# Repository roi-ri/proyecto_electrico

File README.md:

# Proyecto Eléctrico - Ciclador de Baterías

Repositorio integral del proyecto de diseño, construcción y validación de un
ciclador de baterías de propósito múltiple. El proyecto reúne el hardware de
potencia y medición, el firmware de control, el protocolo de comunicación y una
aplicación de escritorio para operar pruebas, visualizar telemetría y exportar
resultados.

## Descripción general

El sistema está orientado a ejecutar pruebas controladas de carga, descarga y
ciclado sobre baterías. La arquitectura combina una PCB dedicada, un ESP32 como
unidad de control y adquisición, sensores de corriente y tensión, y la
aplicación `batView` para supervisar el proceso desde una computadora.

Los objetivos principales del repositorio son:

- Centralizar la documentación técnica y administrativa del proyecto.
- Mantener el diseño eléctrico y los archivos de fabricación de la PCB.
- Versionar el firmware encargado del control y la comunicación.
- Desarrollar la aplicación de escritorio para operación, monitoreo y
  exportación de datos.
- Conservar cronogramas, bitácoras y propuestas como evidencia del avance.

## Componentes del sistema

| Componente | Ubicación | Descripción |
|---|---|---|
| Aplicación de escritorio | `batView/` | Interfaz en C++/wxWidgets para controlar pruebas vía USB/UART, graficar telemetría y exportar resultados. |
| Firmware/control | `code/` | Código en C para control PI, monitoreo de carga/descarga, límites de tensión y comunicación con la PC. |
| PCB | `PCB/` | Proyecto KiCad con esquemático, layout, huellas, símbolos, modelos 3D, salidas e imágenes del diseño. |
| Propuesta | `propuesta/` | Descripción inicial del ciclador, diagramas y documentos de diseño por área. |
| Cronograma | `cronograma/` | Plan de trabajo semanal del proyecto. |
| Bitácoras | `bitácora/` | Registro individual de avances, decisiones y actividades. |

## Estructura del repositorio

```text
proyecto_electrico/
|
├── README.md                         documentación principal del repositorio
├── LICENSE                           licencia MIT del proyecto
├── .gitignore                        reglas generales de archivos ignorados
├── .gitmodules                       submódulos utilizados por el repositorio
|
├── batView/                          aplicación de escritorio del proyecto
│   ├── README.md                     guía técnica de batView
│   ├── CMakeLists.txt                configuración de compilación y pruebas
│   ├── build_app.sh                  build completo para macOS/Linux
│   ├── build_app.ps1                 build completo para Windows
│   ├── install_macos.sh              instalación y empaquetado en macOS
│   ├── install_linux.sh              instalación y empaquetado en Linux
│   ├── install_windows.ps1           instalación y empaquetado en Windows
│   ├── src/                          código fuente de la aplicación
│   ├── tests/                        pruebas unitarias
│   ├── docs/                         documentación de arquitectura e instalación
│   ├── examples/                     firmware de prueba para ESP32
│   ├── scripts/                      automatización de build
│   └── assets/                       iconos e imágenes de la aplicación
|
├── code/                             firmware y control embebido
│   ├── include/                      encabezados del firmware
│   └── src/                          implementaciones en C
|
├── PCB/                              diseño electrónico en KiCad
│   ├── README.md                     documentación de la PCB
│   ├── Proyecto.kicad_pro            archivo principal del proyecto KiCad
│   ├── Proyecto.kicad_sch            esquemático eléctrico
│   ├── Proyecto.kicad_pcb            layout de la PCB
│   ├── symbols/                      símbolos personalizados
│   ├── footprints/                   huellas personalizadas
│   ├── 3dmodels/                     modelos 3D de componentes
│   ├── outputs/                      salidas generadas del diseño
│   └── Imagenes/                     vistas y capturas del diseño
|
├── propuesta/                        propuesta y documentos iniciales
│   ├── propuesta.md                  planteamiento general
│   ├── images/                       diagramas e imágenes de apoyo
│   ├── programa_sw/                  documentación del software
│   ├── protocolo_comunicacion/       documentación del protocolo
│   └── ciclador/                     documentación del ciclador
|
├── cronograma/                       planificación temporal
│   └── cronograma.md                 cronograma semanal
|
└── bitácora/                         bitácoras individuales del equipo
    ├── Brandon.md
    ├── Edu.md
    ├── Jose.md
    ├── Luis.md
    └── Rodrigo.md
```

## Flujo de trabajo del sistema

1. La PCB integra las etapas de potencia, acondicionamiento, sensado y conexión
   con el ESP32.
2. El firmware del ESP32 ejecuta el control de carga/descarga, monitorea
   variables eléctricas y aplica límites de seguridad.
3. La PC se comunica con el ESP32 mediante USB/UART usando tramas de protocolo
   definidas para conexión, configuración, carga, descarga, ciclado y paro.
4. `batView` envía comandos, recibe telemetría, muestra el estado de la prueba,
   grafica mediciones y exporta datos para análisis posterior.

## Protocolo de comunicación

La aplicación y el ESP32 intercambian mensajes de texto con prefijo `#`. Entre
las tramas principales utilizadas por `batView` se encuentran:

- `#CONNECTION`
- `#Battery,<BatteryNameID>,<V@max>,<V@min>,<Amax>`
- `#CICLE,0,0`
- `#CICLE,1,<numeroCiclos>`
- `#LOAD,<0-100>`
- `#UNLOAD,<0-100>`
- `#STOP`
- `#DATA,<tensión>,<corriente>,<timestamp>`

La documentación detallada del protocolo y del flujo de la aplicación se
encuentra en [`batView/README.md`](batView/README.md) y en
[`propuesta/protocolo_comunicacion/`](propuesta/protocolo_comunicacion/).

## Requisitos principales

### Software de escritorio

Para compilar y ejecutar `batView` se requiere, según el sistema operativo:

- CMake.
- Compilador C++ compatible.
- wxWidgets.
- Python 3 y dependencias de empaquetado/exportación.
- Git.

Guías específicas:

- [Instalación en macOS](batView/docs/INSTALL_MACOS.md)
- [Instalación en Linux](batView/docs/INSTALL_LINUX.md)
- [Instalación en Windows](batView/docs/INSTALL_WINDOWS.md)

### Diseño electrónico

Para abrir o modificar la PCB se recomienda:

- KiCad.
- Librerías locales incluidas en `PCB/symbols/`, `PCB/footprints/` y
  `PCB/3dmodels/`.

### Firmware

Para trabajar con el código embebido se recomienda contar con:

- Toolchain compatible con ESP32 o entorno equivalente.
- Acceso al puerto USB/UART del microcontrolador.
- Instrumentación básica para validar tensión, corriente y polaridad antes de
  conectar baterías reales.

## Puesta en marcha rápida

1. Clonar el repositorio:

```bash
git clone <URL_DEL_REPOSITORIO>
cd proyecto_electrico
```

2. Revisar la documentación de la PCB:

```bash
open PCB/README.md
```

3. Entrar a la aplicación de escritorio:

```bash
cd batView
```

4. Ejecutar el instalador correspondiente al sistema:

```bash
./install_macos.sh
```

En Linux:

```bash
./install_linux.sh
```

En Windows:

```powershell
powershell -ExecutionPolicy Bypass -File .\install_windows.ps1
```

## Documentación recomendada

- [`batView/README.md`](batView/README.md): guía principal de la aplicación,
  arquitectura, protocolo, build, pruebas y exportación.
- [`PCB/README.md`](PCB/README.md): descripción de la PCB, conectores, sensores,
  capas y recomendaciones de conexión.
- [`propuesta/propuesta.md`](propuesta/propuesta.md): planteamiento general del
  proyecto.
- [`cronograma/cronograma.md`](cronograma/cronograma.md): actividades planeadas
  por semana.
- [`bitácora/`](bitácora/): seguimiento individual del avance del equipo.

## Estado del proyecto

El repositorio contiene una base funcional y documentada para el desarrollo del
ciclador:

- Aplicación `batView` con conexión serial, flujo guiado de pruebas, gráficas y
  exportación.
- Proyecto KiCad de PCB con documentación visual y descripción de conectores.
- Código de control con módulos separados para comunicación, control PI,
  monitoreo, límites de tensión y paro.
- Documentación académica de propuesta, cronograma y bitácoras.

## Buenas prácticas de uso

- Validar polaridad y niveles de tensión antes de conectar una batería real.
- Probar primero con fuentes limitadas en corriente o cargas controladas.
- Mantener separadas las salidas generadas localmente de los archivos fuente.
- Registrar cambios relevantes en las bitácoras correspondientes.
- Actualizar la documentación cuando se modifique el protocolo, la PCB o el
  flujo de operación de `batView`.

## Licencia

Este proyecto se distribuye bajo licencia MIT. Consulte [`LICENSE`](LICENSE)
para ver los términos completos.

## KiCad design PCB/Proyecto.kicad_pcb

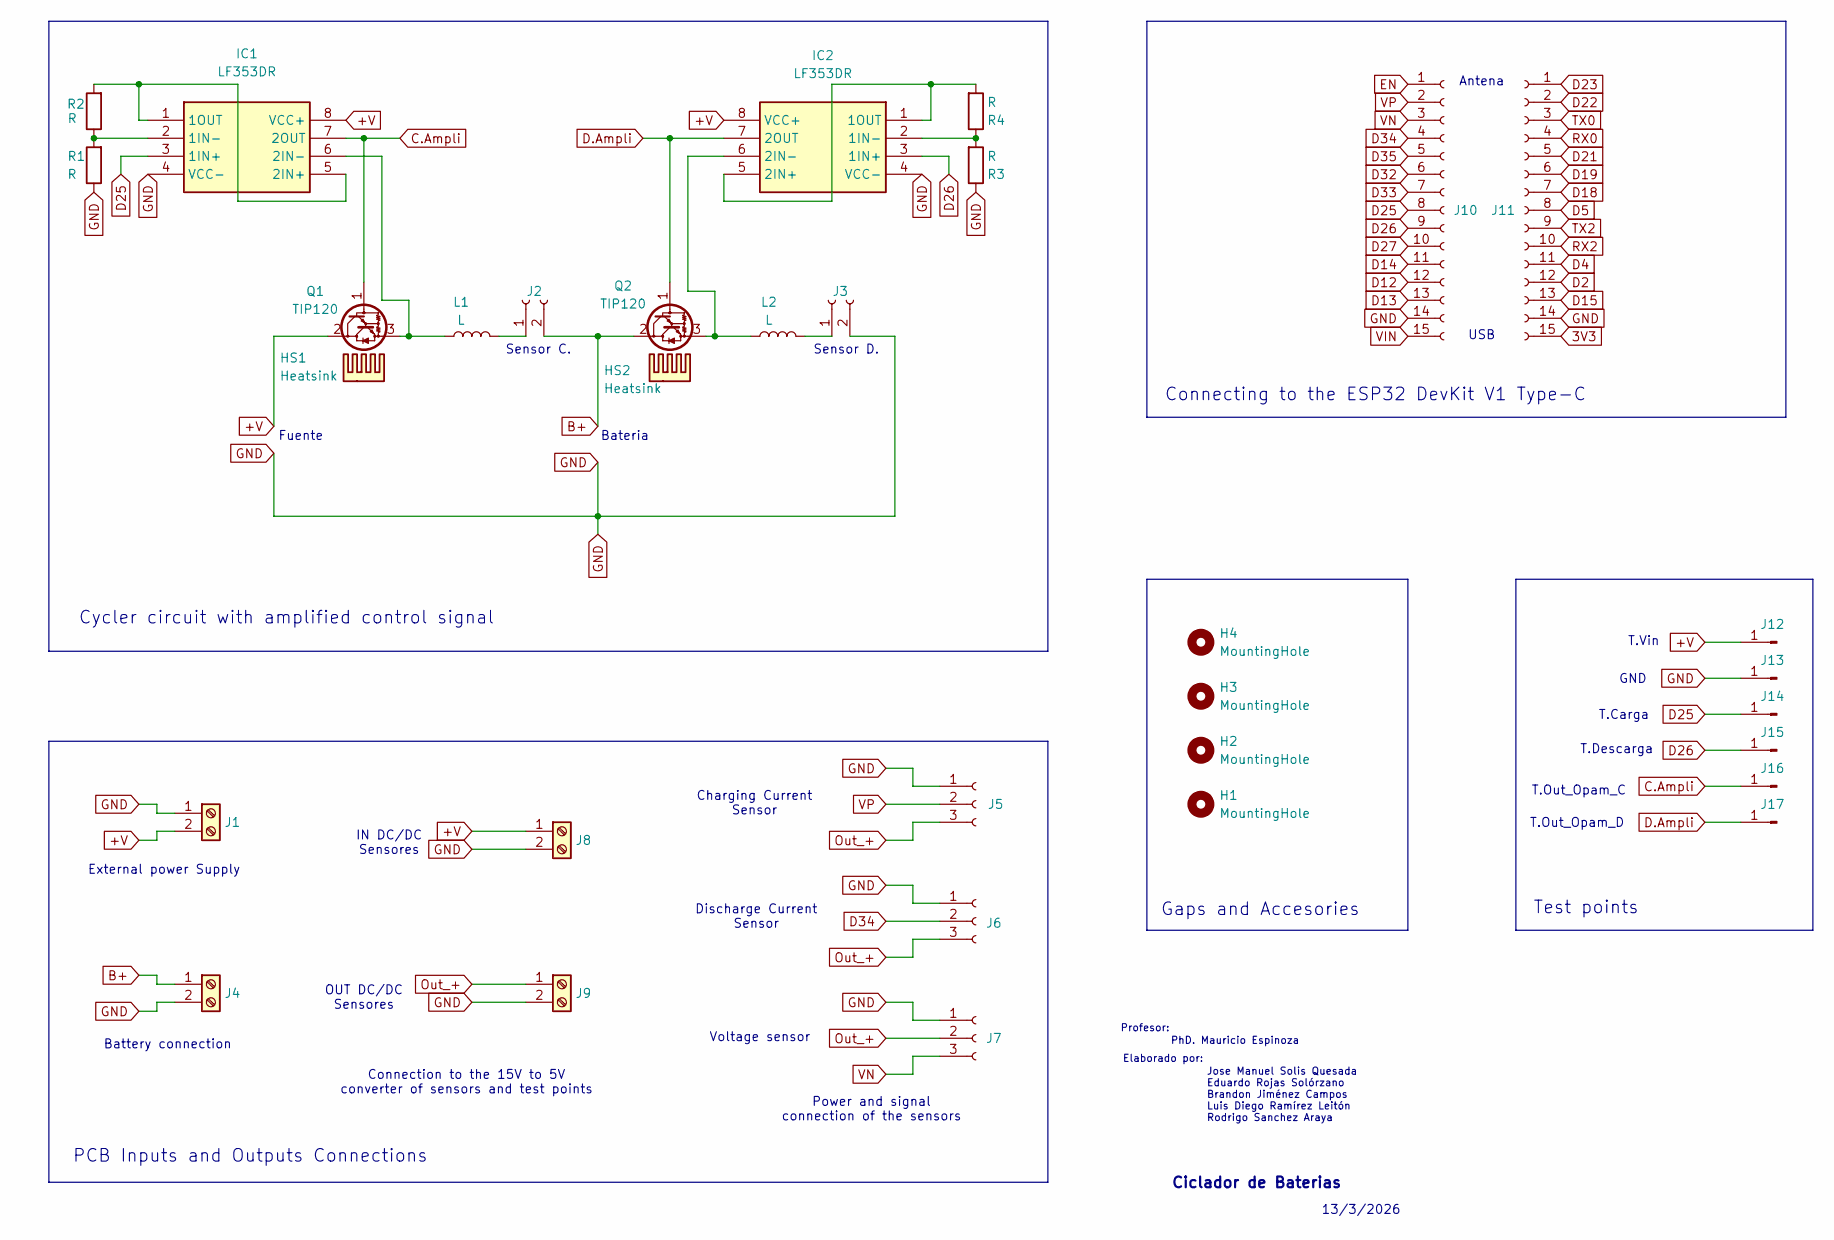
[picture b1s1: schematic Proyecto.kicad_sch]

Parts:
H1, H2, H3, H4: MountingHole; MountingHole_3.2mm_M3
HS1, HS2: Heatsink; Heatsink_TO220_Vert_20x15x11_Pin0
IC1, IC2: LF353DR; SOIC127P600X175-8N; Mouser Part Number 595-LF353DR
J1: Screw_Terminal_01x02; BarrelJack_GCT_DCJ200-10-A_Horizontal
J2, J3: Conn_01x02_Socket; PinSocket_1x02_P2.54mm_Vertical
J4: Screw_Terminal_01x02; TerminalBlock_Phoenix_MKDS-1,5-2_1x02_P5.00mm_Horizontal
J5, J6, J7: Conn_01x03_Socket; PinSocket_1x03_P2.54mm_Vertical
J8, J9: Screw_Terminal_01x02; TerminalBlock_Phoenix_MPT-0,5-2-2.54_1x02_P2.54mm_Horizontal
J10, J11: Conn_01x15_Socket; PinSocket_1x15_P2.54mm_Vertical
J12, J13, J14, J15, J16, J17: Conn_01x01_Pin; TestPoint_Loop_D2.54mm_Drill1.5mm_Beaded
L1, L2: L; L_Radial_D7.8mm_P5.00mm_Fastron_07HCP
Q1, Q2: TIP120; TO-220-3_Vertical
R1, R2, R3, R4: R; R_1206_3216Metric_Pad1.30x1.75mm_HandSolder

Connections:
3V3: J11.15
+V: IC1.8 (VCC+), IC2.8 (VCC+), J1.2, J8.1, J12.1, Q1.2 (C)
B+: J2.2, J4.1, Q2.2 (C)
C.Ampli: IC1.7 (2OUT), J16.1, Q1.1 (B)
D2: J11.12
D4: J11.11
D5: J11.8
D12: J10.12
D13: J10.13
D14: J10.11
D15: J11.13
D18: J11.7
D19: J11.6
D21: J11.5
D22: J11.2
D23: J11.1
D25: IC1.3 (1IN+), J10.8, J14.1
D26: IC2.3 (1IN+), J10.9, J15.1
D27: J10.10
D32: J10.6
D33: J10.7
D34: J6.2, J10.4
D35: J10.5
D.Ampli: IC2.7 (2OUT), J17.1, Q2.1 (B)
EN: J10.1
GND: IC1.4 (VCC-), IC2.4 (VCC-), J1.1, J3.2, J4.2, J5.1, J6.1, J7.1, J8.2, J9.2, J10.14, J11.14, J13.1, R1.1, R3.1
unnamed: IC1.2 (1IN-), R1.2, R2.1
unnamed: IC1.1 (1OUT), IC1.5 (2IN+), R2.2
unnamed: IC1.6 (2IN-), L1.1, Q1.3 (E)
unnamed: IC2.2 (1IN-), R3.2, R4.1
unnamed: IC2.1 (1OUT), IC2.5 (2IN+), R4.2
unnamed: IC2.6 (2IN-), L2.1, Q2.3 (E)
unnamed: J2.1, L1.2
unnamed: J3.1, L2.2
Out_+: J5.3, J6.3, J7.2, J9.1
RX0: J11.4
RX2: J11.10
TX0: J11.3
TX2: J11.9
VIN: J10.15
VN: J7.3, J10.3
VP: J5.2, J10.2

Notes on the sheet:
Jose Manuel Solis Quesada Eduardo Rojas Solórzano Brandon Jiménez Campos Luis Diego Ramírez Leitón Rodrigo Sanchez Araya
Antena
13/3/2026
Charging Current Sensor
Elaborado por:
T.Descarga
Bateria
Sensor D.
T.Out_Opam_C
Profesor:
Cycler circuit with amplified control signal
Ciclador de Baterias
IN DC/DC Sensores
Voltage sensor
Fuente
Sensor C.
GND
PhD. Mauricio Espinoza
Connecting to the ESP32 DevKit V1 Type-C
Battery connection
T.Out_Opam_D
PCB Inputs and Outputs Connections
T.Vin
Connection to the 15V to 5V converter of sensors and test points
T.Carga
Power and signal connection of the sensors
Test points
USB
Discharge Current Sensor
OUT DC/DC Sensores
Gaps and Accesories
External power Supply

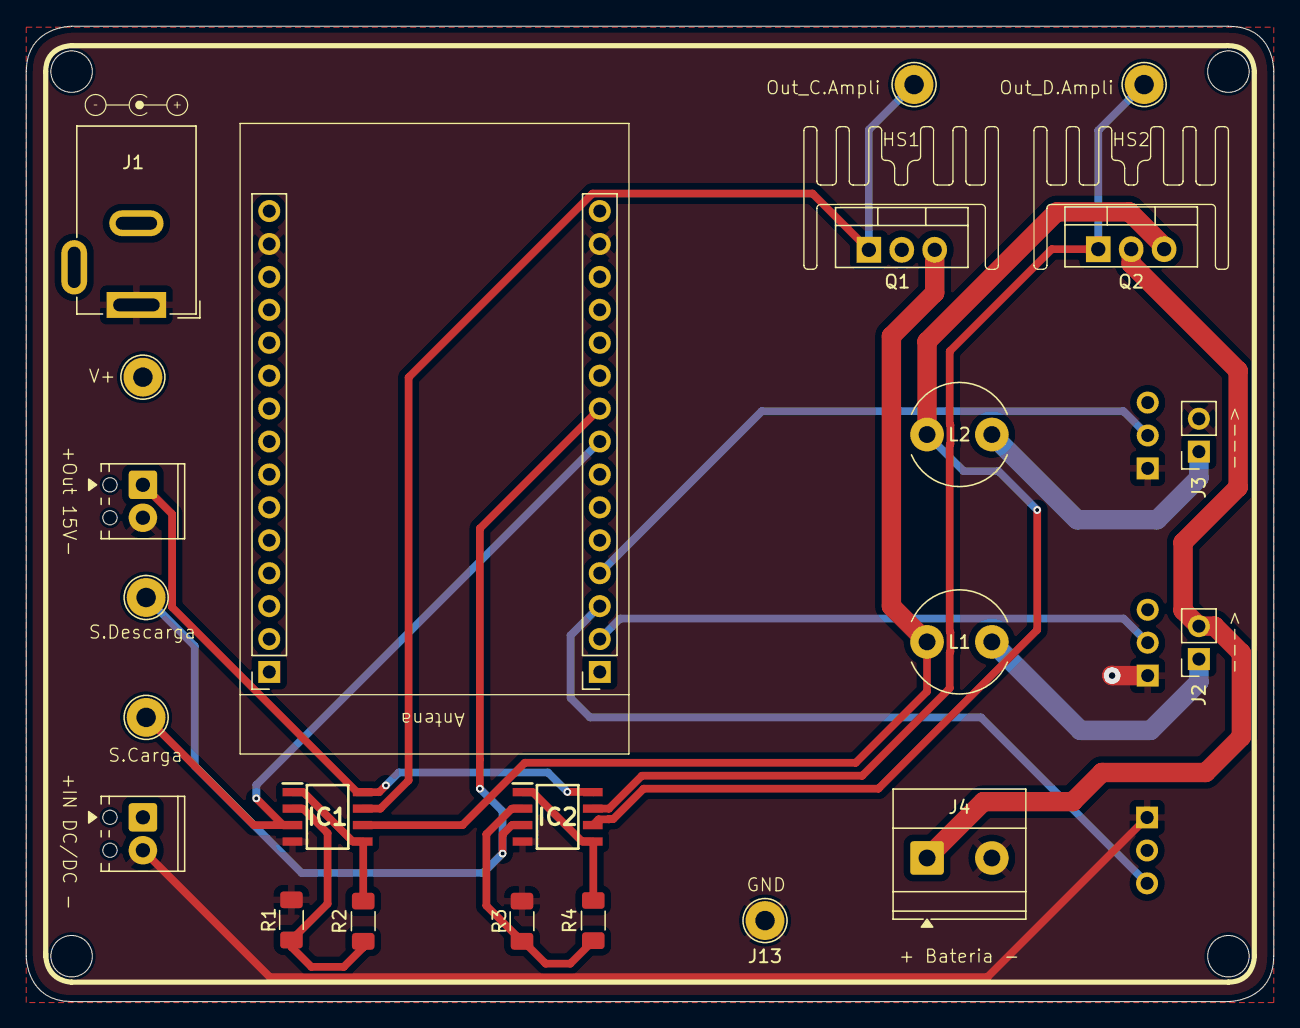
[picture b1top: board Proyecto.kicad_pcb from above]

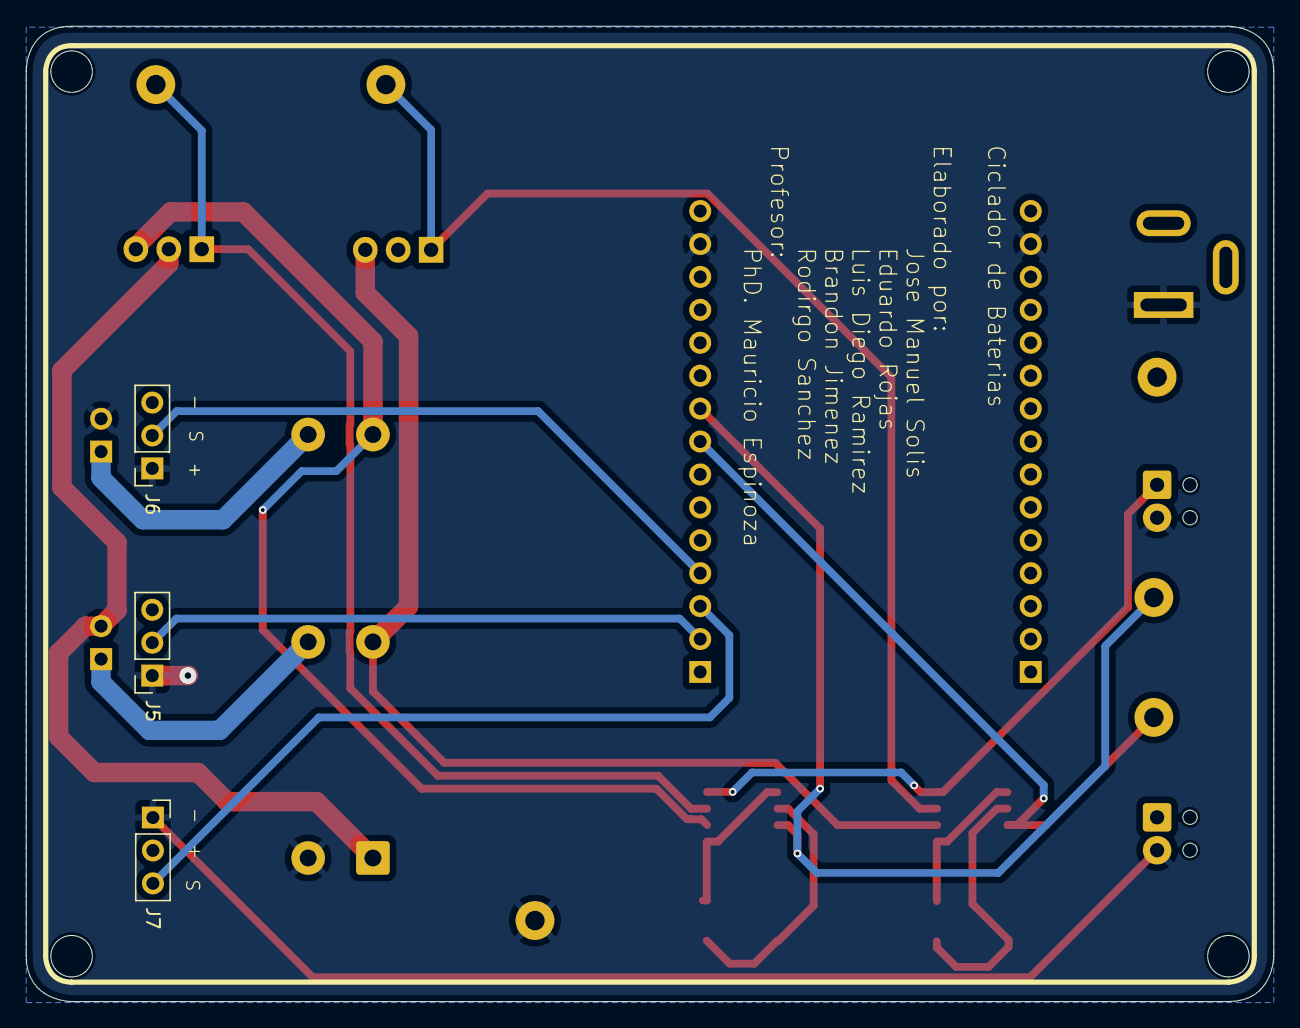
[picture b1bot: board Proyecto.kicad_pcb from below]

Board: 4 copper layers, 96.2 x 75.3 mm, 33 parts (3 on the bottom side), 19 nets.

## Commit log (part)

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2026-02-03 Added: diagrama propuesta
2026-02-04 Added: Directorio para estipular propuesta inicial del ciclador
2026-02-04 Added: Directorio para estipular propuesta inicial del sw
2026-02-04 Added: Directorio para estipular propuesta inicial del protocolo de comunicacion hw <-> sw
2026-02-10 Prueba
2026-02-11 docs: actualizar README con propuesta del ciclador
2026-02-11 docs: añadir README para PCB y PLECS en ciclador
2026-02-11 docs: actualización de README para PCB y PLECS en ciclador
2026-02-17 Added: bitácora para guardar lo que se va haciendo
2026-02-17 Added: branch del ciclador
2026-02-17 Added: Alcances y limitaciones de la aplicación y definición de las arquitecturas para realizar dicho SW
2026-02-17 Added: Arquitectura lógica por capas para la propuesta seleccionada para realizar el SW
2026-02-17 Fix: link formatting in README.md
2026-02-18 Added: Primera actividad realizada en bitácora
2026-02-18 Update link in Rodrigo.md for Propuesta_SW
2026-02-21 Added: link para basar el uso de la GUI con wxWidgets
2026-03-02 Added: Cronograma en el cuál se estarán colocando las actividades esperadas a realizar semana con semana para el pryecto eléctrico
2026-03-02 Fixed: se elimina cronograma de este branch
2026-03-02 Added: cronograma para colocar objetivos a realizar por semana durante el proyecto
2026-03-03 Se agrega la tabla completa, faltan agregar los contenidos
2026-03-03 Added: Se agregan actividades a realizar hasta semana 6
2026-03-09 Added: Se agrega el inicio de la propuesta del protocolo de comu
2026-03-09 Fix: Detalle en título
2026-03-10 Added: Finalización de la propuesta
2026-03-10 feature: Se agrega la bitacora del 10-3-2025
2026-03-10 Feature: Corrección en el formato de la tabla
2026-03-10 Added: Se agrega en la bitácora lo trabajado el día 10 de Marzo
2026-03-10 Added: Se agrega en la bitácora lo trabajado el día 9 de Marzo
2026-03-11 Fixed: Arreglo de tabla de componentes.
2026-03-11 Added: Tabla de presupuestos.
2026-03-11 Fix: Corrección de formato de tabla y actividades
2026-03-15 Added: Bitácora.
2026-03-15 Fixed: Arreglo en la bitácora.
2026-03-15 Fixed: Arreglo en el formato de la fecha de la bitácora.
2026-03-15 Fixed: Arreglos en la bitácora.
2026-03-16 Se agregan los códigos para la obtención de los datos de los sensores
2026-03-16 Fixed: Arreglo en el presupuesto
2026-03-16 Added: sección de requisitos fundamentales y Envío de datos al ESP32
2026-03-17 Added: Se agregan actividades realizadas a la bitácora.
2026-03-17 Fixed: Correción del formato de la tabla la bitácora.
2026-03-17 Fixed: Correción del formato de la tabla.
2026-03-30 Added: Actualización de la bitácora del proyecto
2026-03-30 Fixed: Se corriege el formato de la tabla.
2026-03-31 Added: Uso de WxWidgets para crear apliaciones, utilizando el OS de Mac
2026-04-01 Added: Se agrega propuesta final para la creación del programa de SW
2026-04-01 Added: Redirección en el README hacia el archivo de propuesta final
2026-04-01 Fix link formatting in README.md
2026-04-01 Added: contenido realizado en las últimas semanas a la bitácora
2026-04-02 FIX: Migración a librería actualizada de ESP
2026-04-02 FIX: Se agrega un bitwidth de 12 para mayor seguridad
2026-04-09 Added: Update de la bitácora
2026-04-13 Test: Prueba de orden.
2026-04-13 Fixed: Arreglo en las pruebas.
2026-04-22 Added: estrucutra de la aplicación + segunda y primera capa de integración de esta, con funcionalidades cruciales para la gestión de la adquisisción de datos, la validación del protocolo, la enumerac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
2026-04-22 Se integraron los servicios de adquisición y los paneles para mostrar los resultados en tiempo real. Implementamos las gráficas de voltaje y corriente. Se vinculó el MainViewModel para coordinar la l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
2026-04-22 Delete: Recomenzando el diseño de la App
2026-04-23 Add comprehensive .gitignore file
2026-04-23 Update .gitignore to include more ignored files
    Added additional entries to .gitignore for various files including system files, build artifacts, and temporary files.
2026-04-23 feat: add batView desktop app with serial control, plotting, exports, tests, and packaging
2026-04-23 Added: gitignore
2026-04-23 WIP: guardar cambios antes de rebase
2026-04-23 Make runtime paths portable for assets and exports
2026-04-23 Add Ubuntu build and troubleshooting instructions
2026-04-23 Add cross-platform native packaging pipeline
2026-04-23 Add tag-driven GitHub release workflow
2026-04-23 Add dependency-friendly packaging artifacts
2026-04-23 Move workflows to repository root
2026-04-23 Harden workflow paths for batView builds
2026-04-23 Fix workflow shell and artifact paths
2026-04-23 Fix Windows packaging shell
2026-04-23 Normalize workflow shells and paths
2026-04-23 fixing paths
2026-04-23 Fix packaging workflow paths
2026-04-23 Improve CI wxWidgets setup
2026-04-23 Remove generated build artifacts
2026-04-23 Remove GitHub Actions workflows
2026-04-23 Add cross-platform installation guide
2026-04-23 Split download docs by operating system
2026-04-23 Fix local packaging flow for batView
2026-04-23 Add one-command full batView packaging flow
2026-04-24 batView
2026-04-27 Fixed: Información de la batería.
2026-05-17 feat: Agrega archivo header que contiene la declaración de la función para calcular el voltage de monitoreo.
2026-05-17 feat: Agrega archivo header que contiene la declaración de la función para monitorear la tensión de la batería.
2026-05-18 feat: Se crea la primera versión para el controlador de carga y descarga de la batería.
2026-05-22 ADD: Header file of main functions
2026-05-22 ADD: Header file for PC communication functions
2026-05-22 ADD: Communication code between ESP32 and computer
2026-05-22 ADD: Project main functions
2026-05-22 ADD: Initial main.c
2026-05-24 feat: Crea función para el cálculo de la tensión máxima de carga que se debe monitorear.
2026-05-24 feat: Crea manejo de errores en el porcentaje de carga para el cálculo máximo.
2026-05-24 feat: Crea archivo de cabecera para la función del cálculo de la tensión mínima a donde se va a descargar la batería.
2026-05-24 feat: Crea archivo de la función del cálculo de la tensión mínima a donde se va a descargar la batería.
2026-05-24 fix: Corrige error de argumento en el archivo de cabecera del monitoreo.
2026-05-24 fix: Se elimina la antigua función de monitoreo para dividirla en dos (carga y descarga).
2026-05-24 feat: Crea el archivo de cabecera para la función de monitoreo en carga.
2026-05-24 feat: Crea el archivo de cabecera para la función de monitoreo en descarga.
2026-05-24 feat: Crea función correspondiente al monitoreo para el caso de carga.
2026-05-24 feat: Crea función correspondiente al monitoreo para el caso de descarga.
2026-05-26 feat: Agregan las nuevas funciones en el archvio battery_controller.c.
2026-05-28 ADD: modificación del main_functions implementando las funciones de control
2026-05-28 ADD: Modificación del main_functions.h
2026-06-02 FIX: Arreglados algunos warnings
2026-06-05 Feature: Battery added by GUI, also Fixed windows compiling error
2026-06-05 Added: instalation guides and proper for each OS
2026-06-05 Updated: Instalation instructions
2026-06-06 Updated: app structure files, to match a much more modular style
2026-06-06 Fixed warnings on Linux
2026-06-09 fixed: windows installer not working
2026-06-15 Added: Propuesta del diseño del circuito y la topologia utilizada para el diseño.
2026-06-15 Fix: Corrección en nombre de la imagen del circuito.
2026-06-15 Added: Propuesta del circuito ciclador
2026-06-15 Added: Enlace directo del readme a las diferenctes secciones del diseño del circuito.
2026-06-15 Fix: Corrección de un espacio faltante en el nombre de un enlace.
2026-06-15 feat: Crea la implementación del controlador PI.
2026-06-15 feat: Crea el header file del controlador PI.
2026-06-15 feat: Agrega soporte para los nieveles de tensión que se utilizarán.
2026-06-15 feat: Cambia y agrega una corriente de referencia en el argumento.
2026-06-15 docs: Cambia la explicación de las entradas.
2026-06-15 feat: Agrega soporte para el argumento que se agregó.
2026-06-15 feat: Agrega implementación del controlador PI y stop_charge en el principal de la parte de control.
2026-06-15 docs: Agrega documentación y cambia nombre a stop_load para mantener estándar.
2026-06-15 gefeat: Crea la implementación de la función de detener la carga.
2026-06-16 Added: Función de transferencia del circuito.
2026-06-16 Fix: Se corriege el formato de los titulos.
2026-06-16 Fix: Se corriege el formato de las ecuaciones que generaban error.
2026-06-16 Added: Titulo a la función de transferencia.
2026-06-16 Added: Simulación del sistema de control en Plecs y circuito emulador de la PCB par apruebas de hardware in the loop
2026-06-18 Fix: Cambio de nombre de Diseño.md a README.md
2026-06-18 Added: Función de transferencia del circuito de descarga.
2026-06-18 Added: Descripción de las simulaciones implementadas en plecs para verificar el control y para hardware in the loop.
2026-06-18 Added: Se agrega el directorio con las imagenes de la explicación de las simulaciones para mostrar los resutlados
2026-06-18 Fix: Coerrección en el formato del diagrama de bloques.
2026-06-18 Fix: Coerrección de una letra en el codigo del diagrama de bloques.
2026-06-24 Improve Windows installation guide
2026-06-24 Fix Windows installer winget source handling
2026-06-24 Support Windows ARM64 install triplet
2026-06-24 Fix Windows ARM64 build tools setup
2026-06-24 Use x64 Windows triplet by default on ARM
2026-06-24 Set vcpkg host triplet on Windows ARM
2026-06-24 Find Python after Windows dependency install
2026-06-24 Build x64 app correctly on Windows ARM
2026-06-24 Detect Python executable architecture on Windows
2026-06-25 Modification of battery controller due to the interface update
2026-06-25 Modification of comm_with_pc due to the interface update
2026-06-25 Modification of main_functions due to the interface update
2026-06-25 Modification of main due to the interface update
2026-06-25 Modification of stop_load to the interface update
2026-06-25 Modification of the header file battery_controller due to the interface update
2026-06-25 Modification of the header file comm_with_pc due to the interface update
2026-06-25 Modification of the header file main_functions due to the interface update
2026-06-25 Fix: Port correction
2026-06-25 FIX: Timing
2026-06-25 Fix: Problems with STOP
2026-06-25 FIX: Problems with the ACK, connection
2026-06-25 FIX: Problems with the STOP
2026-06-26 Added: Fixes and features to the batView Graphication mode and other GUI improvements
2026-06-26 Added: Esquematico, editor de placa y archivos de fabricación de la PCB con sus repectivas dependencias de simbolos y modelos 3D utilizados para la elebarocación del prototipo.
2026-06-26 DOCS: Agregar documentación e imágenes de la PCB
2026-06-26 Fix: Corrección en la descripción de la PCB.
2026-06-27 Fix: Corrección en los diagramas de la expliciación.
2026-06-27 Fix: Corrección en el formato de los diagramas
2026-06-27 Fix: Se reduce el texto y se quietan unos diagramas.
2026-06-27 Fix: Remove DS_Store files
2026-06-28 Final Version batView
2026-06-28 Added: Versión final de la simulación hardware un the loop
2026-06-28 Added: Configuración de pines para hardware in the loop
2026-06-28 Fixed: Se elimina todo lo relacionado a simular la bateria en un microcontrolador.
2026-06-28 Update: Se actualiza la lista de componentes.
2026-06-28 Fixed: Arreglo en la lista de componentes.
2026-06-28 Fixed: Se arregla nombre de documento.
2026-06-28 FIX: New parameters kp and ki
2026-06-28 FIX: Battery controller bug in cicle
2026-06-28 FIX: Adapted to the new protocol betwen ESP and PC
2026-06-28 FIX: Bugs in connection and desconnection
2026-06-28 FIX: Now it uses the max and min values provided through the interface
2026-06-28 FIX: It uses the max value provided through the interface
2026-06-28 ADD: New functions to help the PI
2026-06-28 FIX: New parameters to functions
2026-06-29 Fixed: Se coloca el directorio de PCB fuera de la propuesta representando un entregable.
2026-06-29 Added: Bitácora final del proyecto de Jose Manuel Solis - C27645
2026-06-30 Adjust battery life calculation by discharge count
